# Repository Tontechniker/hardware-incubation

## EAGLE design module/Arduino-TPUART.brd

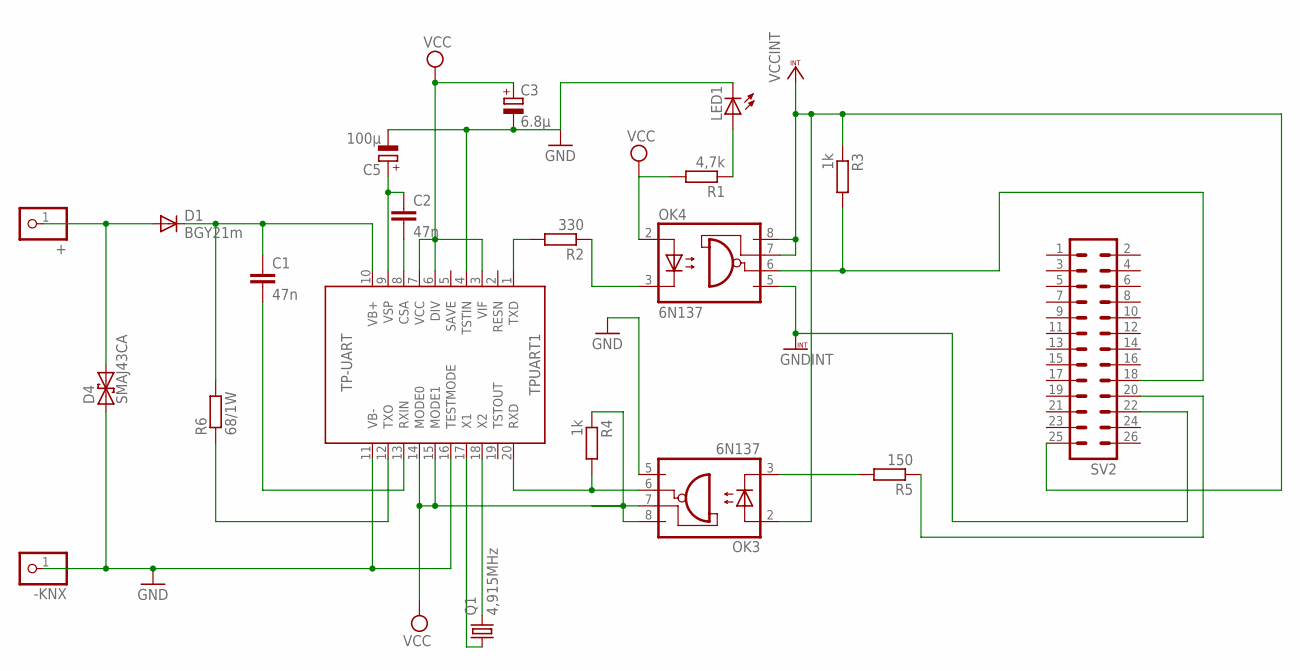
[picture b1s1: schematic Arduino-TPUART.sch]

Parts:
+: PINHD-1X1; 1X01
-KNX: PINHD-1X1; 1X01
C1, C2: 47n; C1206
C3: 6.8µ; CT7343
C5: 100µ; CT7343
D1: BGY21m; SMB
D4: SMAJ43CA; DO214AA
LED1: LEDKA-3528ASYC; KA-3528ASYC
OK3, OK4: 6N137; DIL8-SMD
Q1: 4,915MHz; HC49UP
R1: 4,7k; M1206
R2: 330; M1206
R3, R4: 1k; M1206
R5: 150; M1206
R6: 68/1W; R2512
SV2: MA13-2
TPUART1: TP-UART; SOIC20

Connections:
ARDUINO_RXD: OK4.6 (VO), R3.2, SV2.18
GND: -KNX.1, C3.-, C5.-, D4.A (1), LED1.C, OK3.5 (GND), TPUART1.4 (TSTIN), TPUART1.11 (VB-), TPUART1.16 (TESTMODE)
GNDINT: OK4.5 (GND), SV2.22
KNX+: +.1, D1.A, D4.C (2)
unnamed: C1.1, D1.C, R6.2, TPUART1.10 (VB+)
unnamed: R6.1, TPUART1.12 (TXO)
unnamed: C1.2, TPUART1.13 (RXIN)
unnamed: C2.2, TPUART1.8 (CSA)
unnamed: C2.1, C5.+, TPUART1.9 (VSP)
unnamed: Q1.1, TPUART1.17 (X1)
unnamed: Q1.2, TPUART1.18 (X2)
unnamed: R2.2, TPUART1.1 (TXD)
unnamed: OK4.3 (C), R2.1
unnamed: R5.1, SV2.20
unnamed: OK3.6 (VO), R4.2, TPUART1.20 (RXD)
unnamed: OK3.3 (C), R5.2
unnamed: LED1.A, R1.1
VCC: C3.+, OK3.7 (VE), OK3.8 (VCC), OK4.2 (A), R1.2, R4.1, TPUART1.3 (VIF), TPUART1.6 (DIV), TPUART1.7 (VCC), TPUART1.14 (MODE0), TPUART1.15 (MODE1)
VCCINT: OK3.2 (A), OK4.7 (VE), OK4.8 (VCC), R3.1, SV2.25

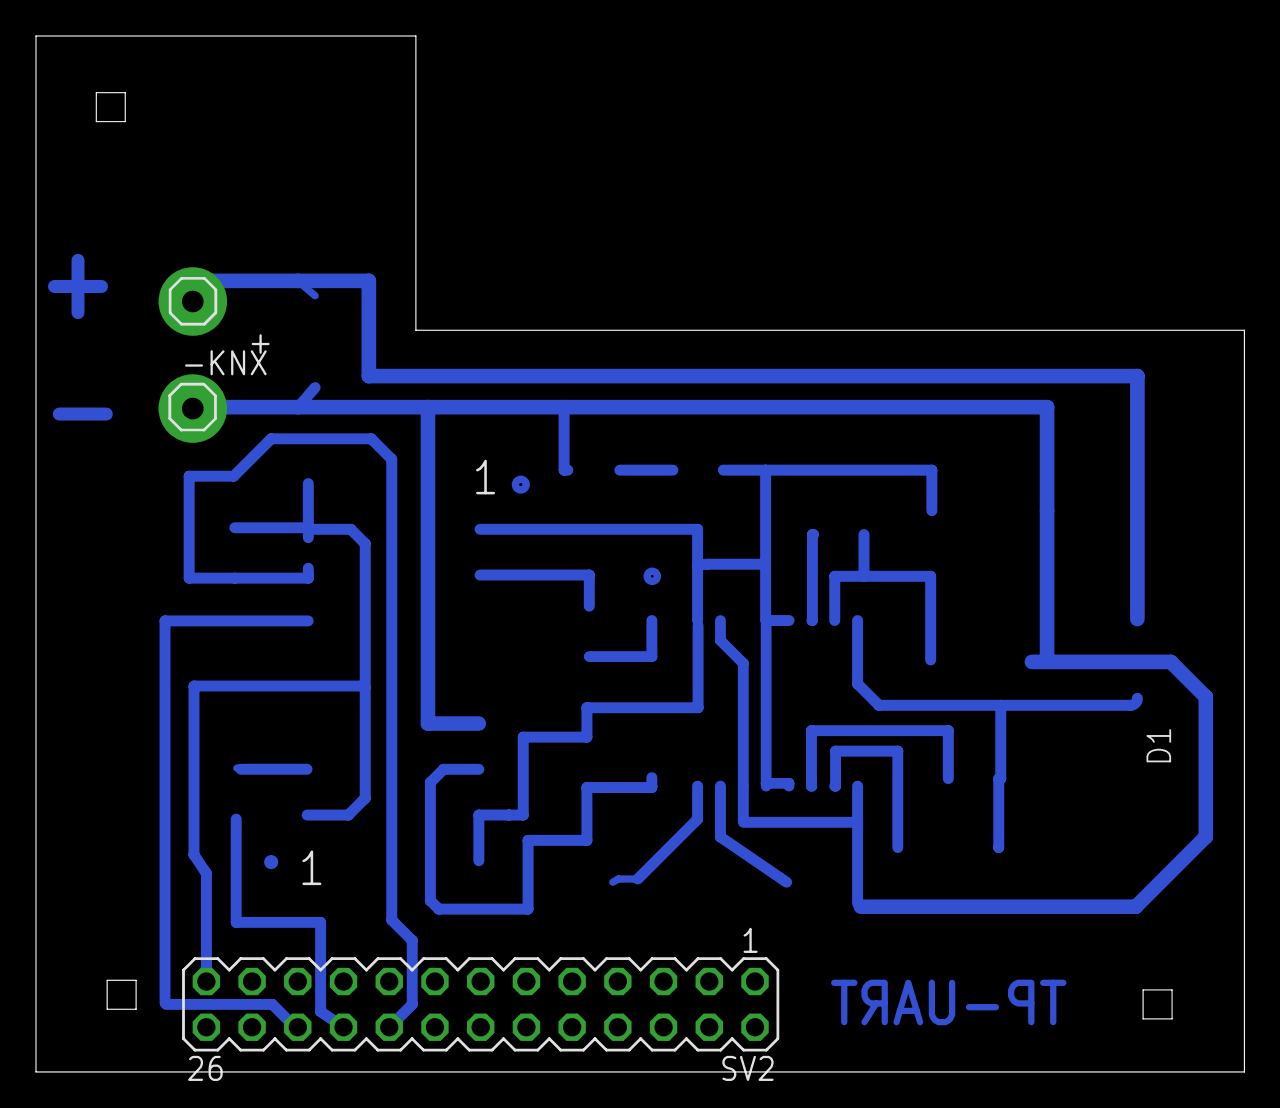
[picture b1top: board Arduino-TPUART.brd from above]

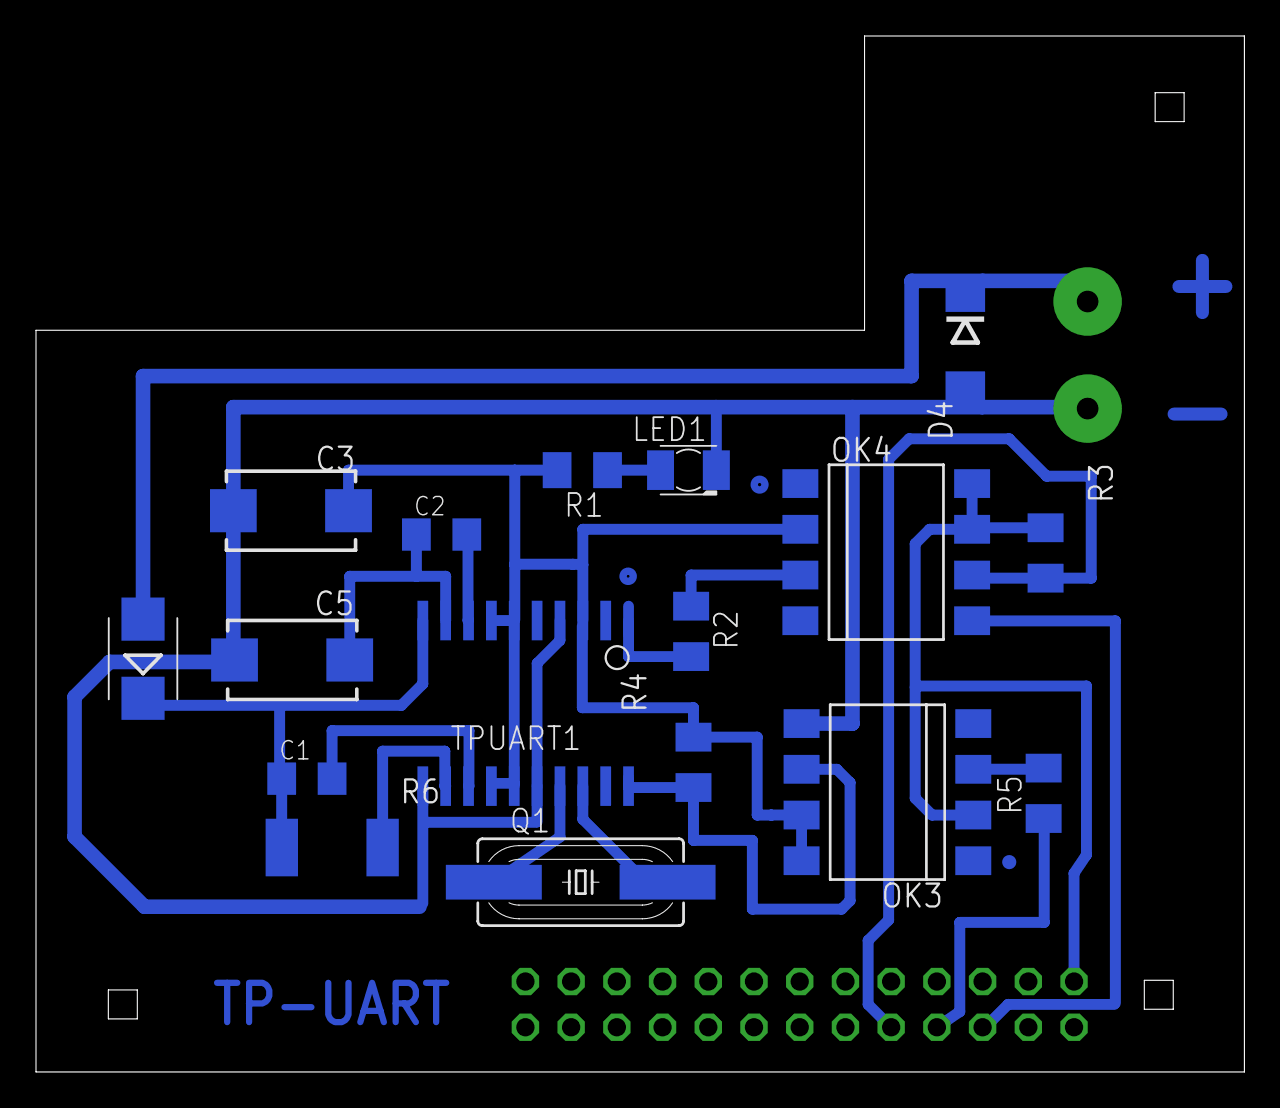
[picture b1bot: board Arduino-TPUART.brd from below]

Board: 2 copper layers, 67.1 x 57.6 mm, 20 parts (17 on the bottom side), 19 nets.

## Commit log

2018-03-06 Create TPUART Interface Raspberry Pi
2018-03-07 Create TPUART for Raspi
